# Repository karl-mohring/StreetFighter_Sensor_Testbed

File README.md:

# StreetFighter - Smart Streetlight Testbed

# What is it?
StreetFighter is a smart cities sensor platform intended for mounting inside LED street lights. The platform includes sensors to monitor road usage, and can manage street light dimming to adapt the light level to real-time traffic.

## Why the stupid name?
- The main hardware platform of this project is the Arduino **Yun**.
- **Yun** (Lee) is a character from CAPCOM's **Street Fighter** franchise.
- Our sensor platform is intended for road-side deployment in **street** lights to **fight** energy waste
- It made sense to me...

# [Quick Start](https://github.com/Leenix/StreetFighter_Sensor_Testbed/wiki/Hardware-Installation)
The phrase "quick-start" can be misleading in hardware projects, but here's a list of things you'll need to set up this platform [(Full details in the Wiki)](https://github.com/Leenix/StreetFighter_Sensor_Testbed/wiki):
- Arduino Yun (with 4GB card) or Arduino Leonardo (for the non-logging, non-WiFi version)
- StreetFighter PCB
- Traffic sensors (sonar, lidar, PIR)
- Environmental sensors (temperature, humidity, illuminance, IR temperature, noise)
- Some kind of long-range network transceiver (XBee socket)

After you get all all that, you just need to populate the PCBs, wire up the sensors, configure the Yun software, build and upload the Arduino-side firmware, power the platform somehow, and then you're golden.

# [Features](https://github.com/Leenix/StreetFighter_Sensor_Testbed/wiki/Features)
## Traffic detection
- PIR sensor detects generic movements from vehicles, cyslists, and pedestrians
- Sonar/Lidar counts vehicles over a single lane

## Environmental monitoring
- Ambient temperature
- Relative humidity
- Illuminance
- Ambient noise
- Road temperature
- Road flood level

## Lamp health and control
- Luminaire temperature
- Power consumption
- Dimming interface

## Other
- Smartphone detection using Wifi and/or Bluetooth
- Public WiFi AP (if wired connection is provided)

# [Documentation](https://github.com/Leenix/StreetFighter_Sensor_Testbed/wiki)
- Full installation documentation can be found on the [Wiki](https://github.com/Leenix/StreetFighter_Sensor_Testbed/wiki)
- Code documentation is inside the code. No external reference just yet.

# [License](http://www.gnu.org/licenses/gpl-3.0.en.html)

This project is licensed under the terms of the GNU General Public License v3.0.

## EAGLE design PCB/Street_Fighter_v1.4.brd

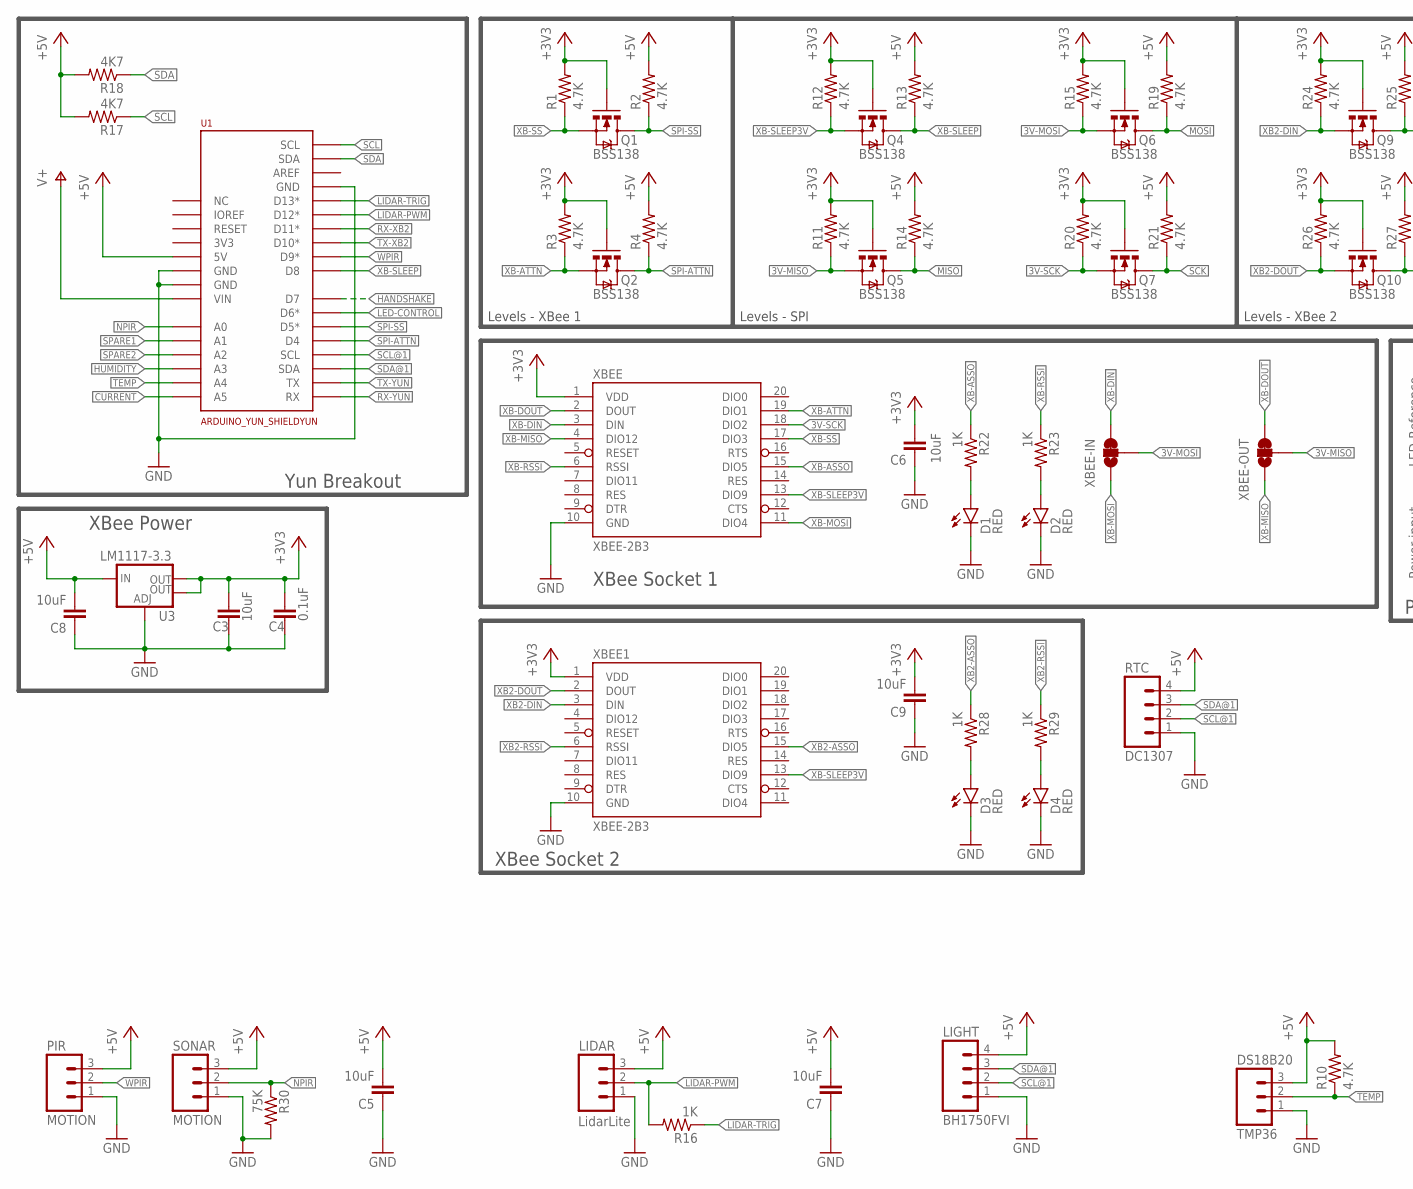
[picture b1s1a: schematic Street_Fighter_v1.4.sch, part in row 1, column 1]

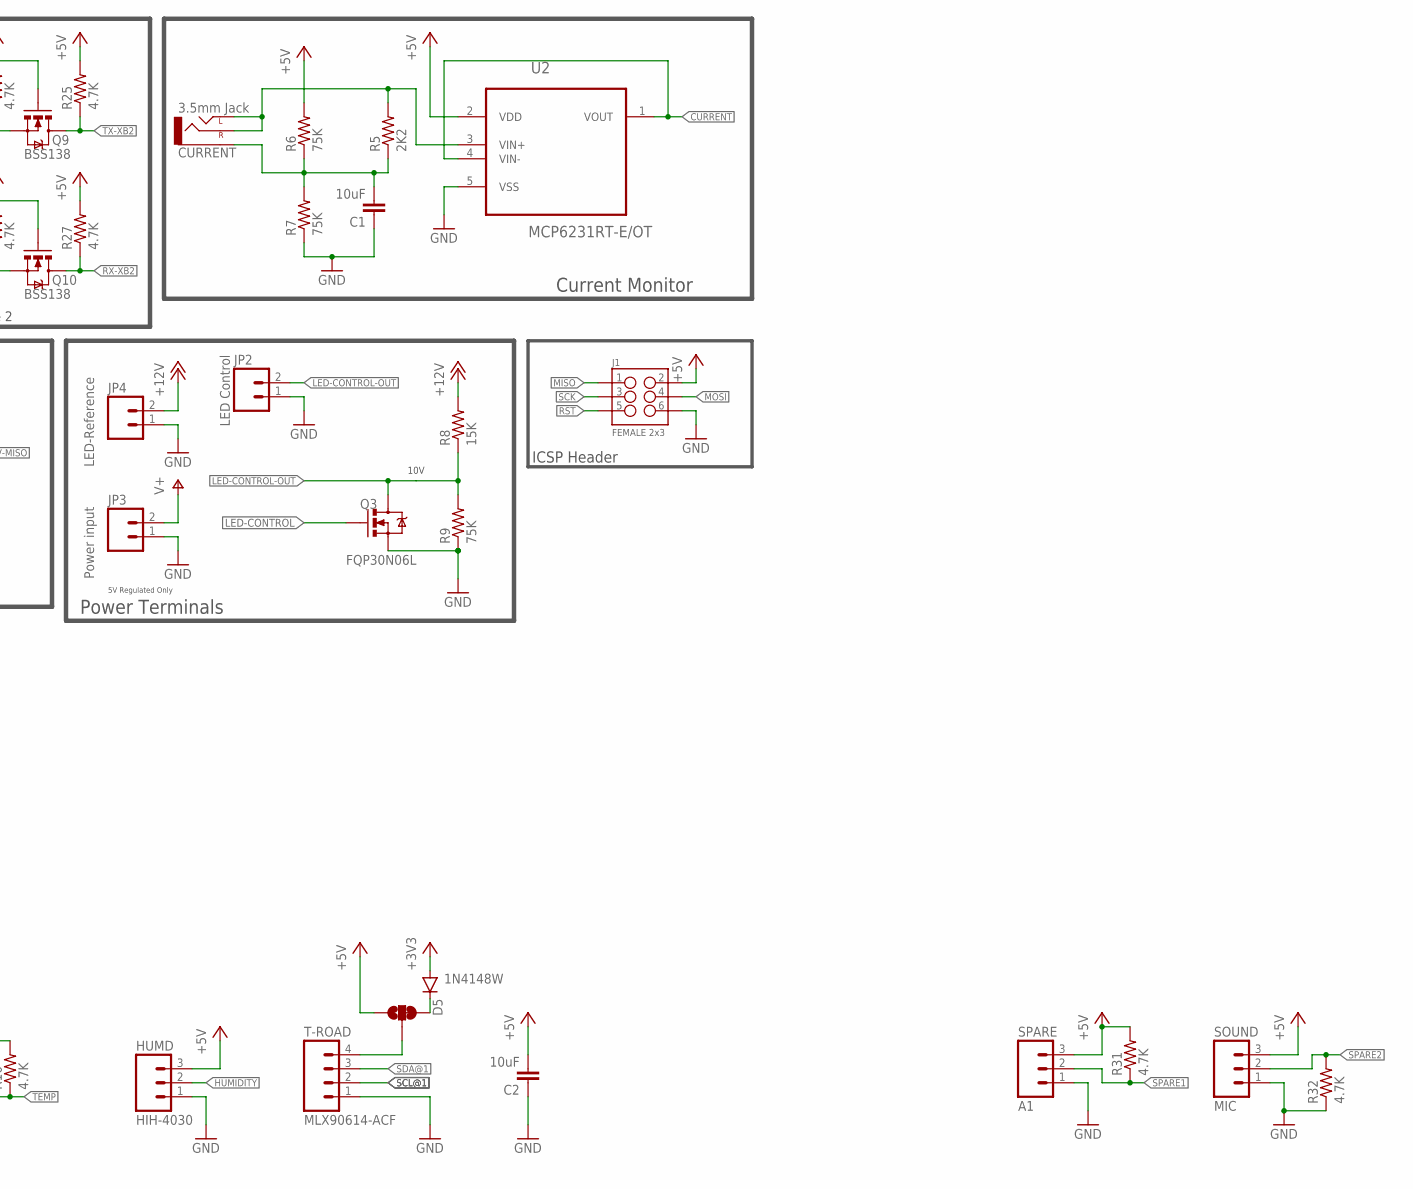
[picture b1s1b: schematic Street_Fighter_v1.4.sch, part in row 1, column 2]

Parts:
C1, C2, C3, C5, C6, C7, C8, C9: 10uF; 1206
C4: 0.1uF; 1206
CURRENT: 3.5mm Jack; AUDIO-JACK
D1, D2, D3, D4: RED; LED-1206
D5: 1N4148W; SOD-123
DS18B20: TMP36; 1X03
HUMD: HIH-4030; 1X03
J1: FEMALE 2x3; 2X3
JP2: LED Control; 1X02_LONGPADS
JP3: Power input; 1X02_LONGPADS
JP4: LED-Reference; 1X02_LONGPADS
LIDAR: LidarLite; 1X03
LIGHT: BH1750FVI; 1X04
PIR: MOTION; 1X03
Q1, Q2, Q4, Q5, Q6, Q7, Q9, Q10: BSS138; SOT23
Q3: FQP30N06L; TO220V
R1, R2, R3, R4, R10, R11, R12, R13, R14, R15, R19, R20, R21, R24, R25, R26, R27, R31, R32: 4.7K; 1206
R5: 2K2; 1206
R6, R7, R9, R30: 75K; 1206
R8: 15K; 1206
R16, R22, R23, R28, R29: 1K; 1206
R17, R18: 4K7; 1206
RTC: DC1307; 1X04
SONAR: MOTION; 1X03
SOUND: MIC; 1X03
SPARE: A1; 1X03
T-ROAD: MLX90614-ACF; 1X04
U1: ARDUINO_YUN_SHIELDYUN; DUEMILANOVE_VIAS
U2: MCP6231RT-E/OT; SOT95P270X145-5N
U3: LM1117-3.3; SOT223
XBEE, XBEE1: XBEE-2B3; XBEE-SMD
XBEE-IN: JUMPER-PAD-3-2OF3_NC_BY_TRACE_SMALL; PAD-JUMPER-3-2OF3_NC_BY_TRACE_YES_SILK_FULL_BOX
XBEE-OUT, XBEE-OUT1: JUMPER-PAD-3-2OF3_NC_BY_TRACE_SMALL; PAD-JUMPER-3-2OF3_NC_BY_TRACE_YES_SILK_FULL_BOX

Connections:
3V3: U1.3V3
3V-MISO: Q5.2 (S), R11.1, XBEE-OUT.2
3V-MOSI: Q6.2 (S), R15.1, XBEE-IN.2
3V-SCK: Q7.2 (S), R20.1, XBEE.18 (DIO2)
+3V3: C3.2, C4.2, C6.2, C9.2, D5.A, Q1.1 (G), Q2.1 (G), Q4.1 (G), Q5.1 (G), Q6.1 (G), Q7.1 (G), Q9.1 (G), Q10.1 (G), R1.2, R3.2, R11.2, R12.2, R15.2, R20.2, R24.2, R26.2, U3.2 (OUT), U3.4 (OUT), XBEE.1 (VDD), XBEE1.1 (VDD)
+5V: C2.2, C5.2, C7.2, C8.2, DS18B20.3, HUMD.3, J1.2, LIDAR.3, LIGHT.4, PIR.3, R2.2, R4.2, R6.2, R10.2, R13.2, R14.2, R17.2, R18.2, R19.2, R21.2, R25.2, R27.2, R31.2, RTC.4, SONAR.3, SOUND.3, SPARE.3, U1.5V, U2.2 (VDD), U3.3 (IN), XBEE-OUT1.1
+12V: JP4.2, R8.2
CURRENT: U1.A5, U2.1 (VOUT), U2.4 (VIN-)
GND: C1.1, C2.1, C3.1, C4.1, C5.1, C6.1, C7.1, C8.1, C9.1, D1.C, D2.C, D3.C, D4.C, DS18B20.1, HUMD.1, J1.6, JP2.1, JP3.1, JP4.1, LIDAR.1, LIGHT.1, PIR.1, Q3.3 (S), R7.1, R9.1, R30.2, R32.1, RTC.1, SONAR.1, SOUND.1, SPARE.1, T-ROAD.1, U1.GND, U1.GND@0 (GND), U1.GND@1 (GND), U2.5 (VSS), U3.1 (ADJ), XBEE.10 (GND), XBEE1.10 (GND)
HANDSHAKE: U1.7 (D7)
HUMIDITY: HUMD.2, U1.A3
LED-CONTROL: Q3.1 (G), U1.6 (D6*)
LED-CONTROL-OUT: JP2.2, Q3.2 (D), R8.1, R9.2
LIDAR-PWM: LIDAR.2, R16.2, U1.12 (D12*)
LIDAR-TRIG: R16.1, U1.13 (D13*)
MISO: J1.1, Q5.3 (D), R14.1
MOSI: J1.4, Q6.3 (D), R19.1
unnamed: D1.A, R22.2
unnamed: CURRENT.RING (RIGHT), CURRENT.TIP (LEFT), R5.2, U2.3 (VIN+)
unnamed: D2.A, R23.2
unnamed: C1.2, CURRENT.SLEEVE, R5.1, R6.1, R7.2
unnamed: D3.A, R28.2
unnamed: D4.A, R29.2
unnamed: D5.C, XBEE-OUT1.3
unnamed: T-ROAD.4, XBEE-OUT1.2
NPIR: R30.1, SONAR.2, U1.A0
RST: J1.5
RX-XB2: Q10.3 (D), R27.1, U1.11 (D11*)
RX-YUN: U1.0 (RX)
SCK: J1.3, Q7.3 (D), R21.1
SCL: R17.1, U1.3@1 (SCL)
SCL@1: LIGHT.2, RTC.2, T-ROAD.2, U1.3 (SCL)
SDA: R18.1, U1.2@1 (SDA)
SDA@1: LIGHT.3, RTC.3, T-ROAD.3, U1.2 (SDA)
SPARE1: R31.1, SPARE.2, U1.A1
SPARE2: R32.2, SOUND.2, U1.A2
SPI-ATTN: Q2.3 (D), R4.1, U1.D4
SPI-SS: Q1.3 (D), R2.1, U1.5 (D5*)
TEMP: DS18B20.2, R10.1, U1.A4
TX-XB2: Q9.3 (D), R25.1, U1.10 (D10*)
TX-YUN: U1.1 (TX)
V+: JP3.2, U1.VIN
WPIR: PIR.2, U1.9 (D9*)
XB2-ASSO: R28.1, XBEE1.15 (DIO5)
XB2-DIN: Q9.2 (S), R24.1, XBEE1.3 (DIN)
XB2-DOUT: Q10.2 (S), R26.1, XBEE1.2 (DOUT)
XB2-RSSI: R29.1, XBEE1.6 (RSSI)
XB-ASSO: R22.1, XBEE.15 (DIO5)
XB-ATTN: Q2.2 (S), R3.1, XBEE.19 (DIO1)
XB-DIN: XBEE.3 (DIN), XBEE-IN.3
XB-DOUT: XBEE.2 (DOUT), XBEE-OUT.3
XB-MISO: XBEE.4 (DIO12), XBEE-OUT.1
XB-MOSI: XBEE.11 (DIO4), XBEE-IN.1
XB-RSSI: R23.1, XBEE.6 (RSSI)
XB-SLEEP: Q4.3 (D), R13.1, U1.8 (D8)
XB-SLEEP3V: Q4.2 (S), R12.1, XBEE.13 (DIO9), XBEE1.13 (DIO9)
XB-SS: Q1.2 (S), R1.1, XBEE.17 (DIO3)

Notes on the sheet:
10V
Power Terminals
Yun Breakout
Current Monitor
XBee Socket 1
5V Regulated Only
Levels - XBee 1
Levels - SPI
Levels - XBee 2
XBee Power
XBee Socket 2
ICSP Header

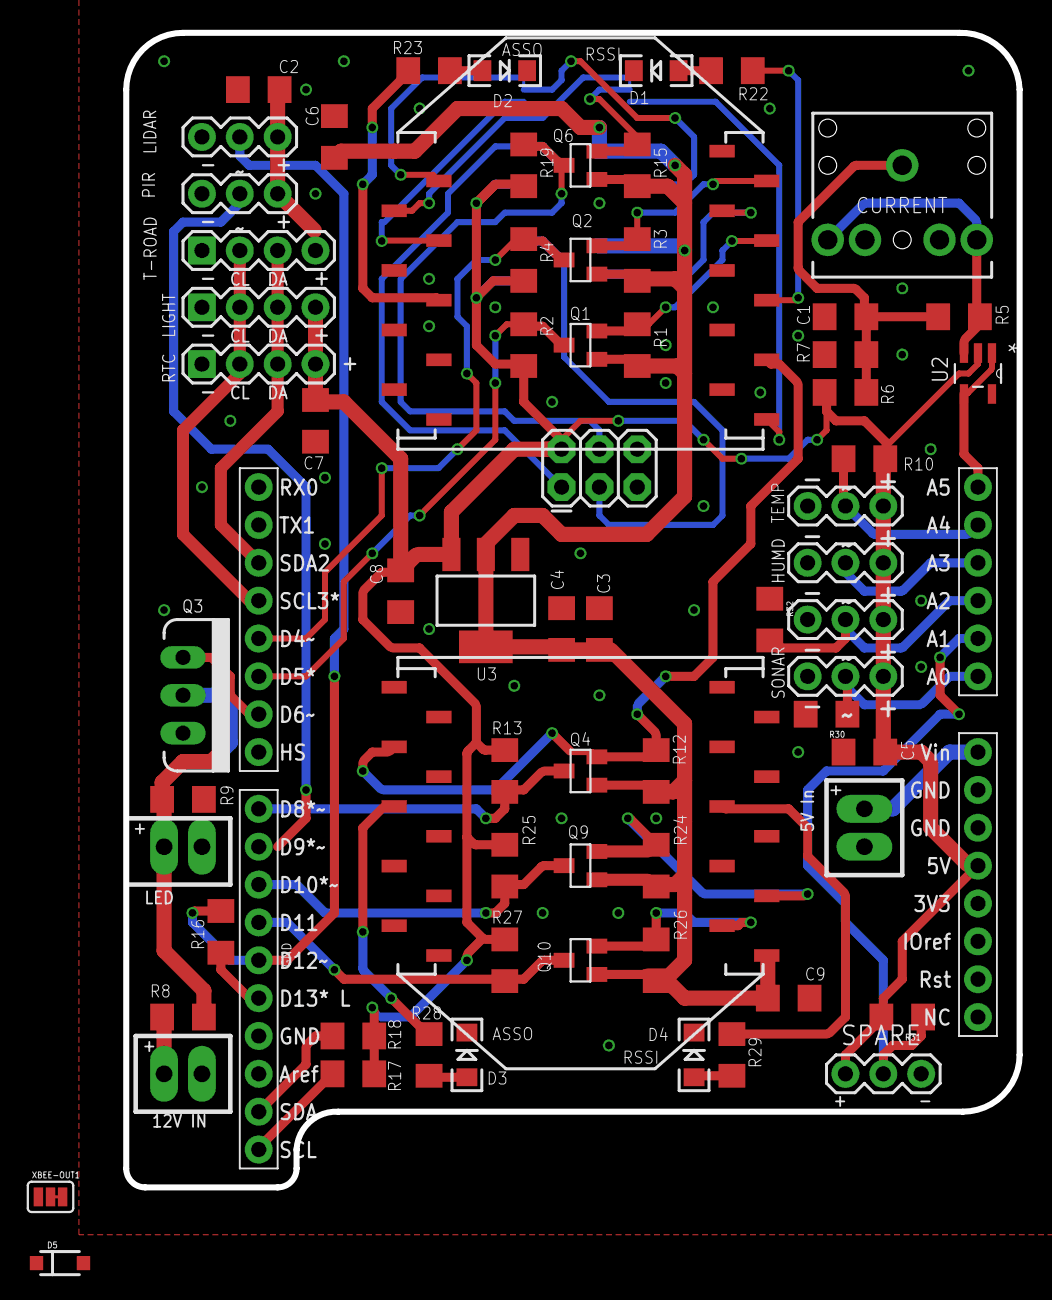
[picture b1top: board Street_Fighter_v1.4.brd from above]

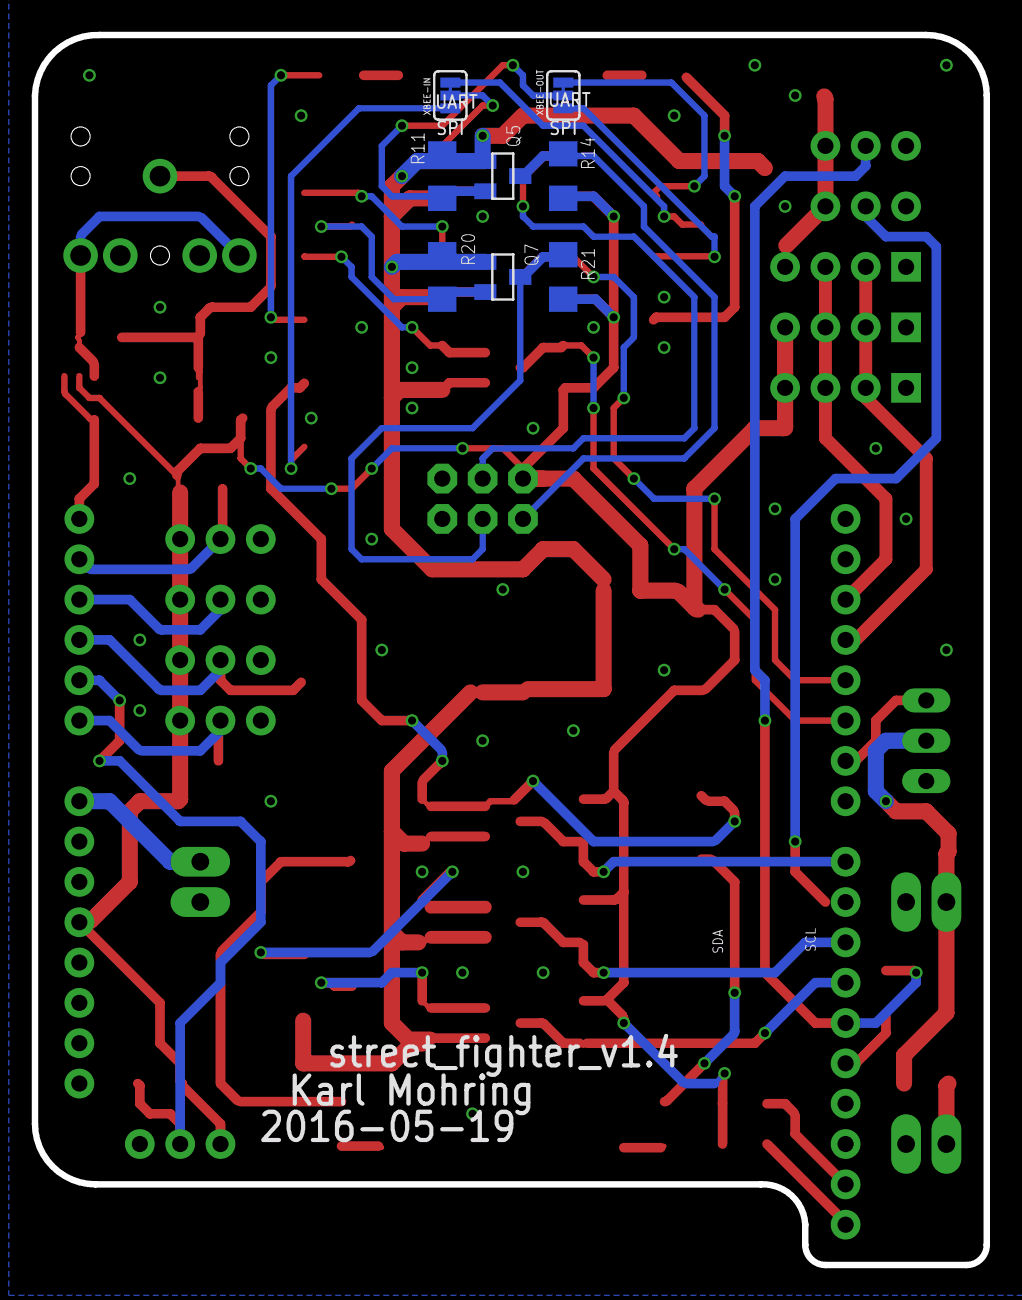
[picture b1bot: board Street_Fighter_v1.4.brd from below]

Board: 2 copper layers, 59.9 x 77.5 mm, 78 parts (8 on the bottom side), 52 nets.

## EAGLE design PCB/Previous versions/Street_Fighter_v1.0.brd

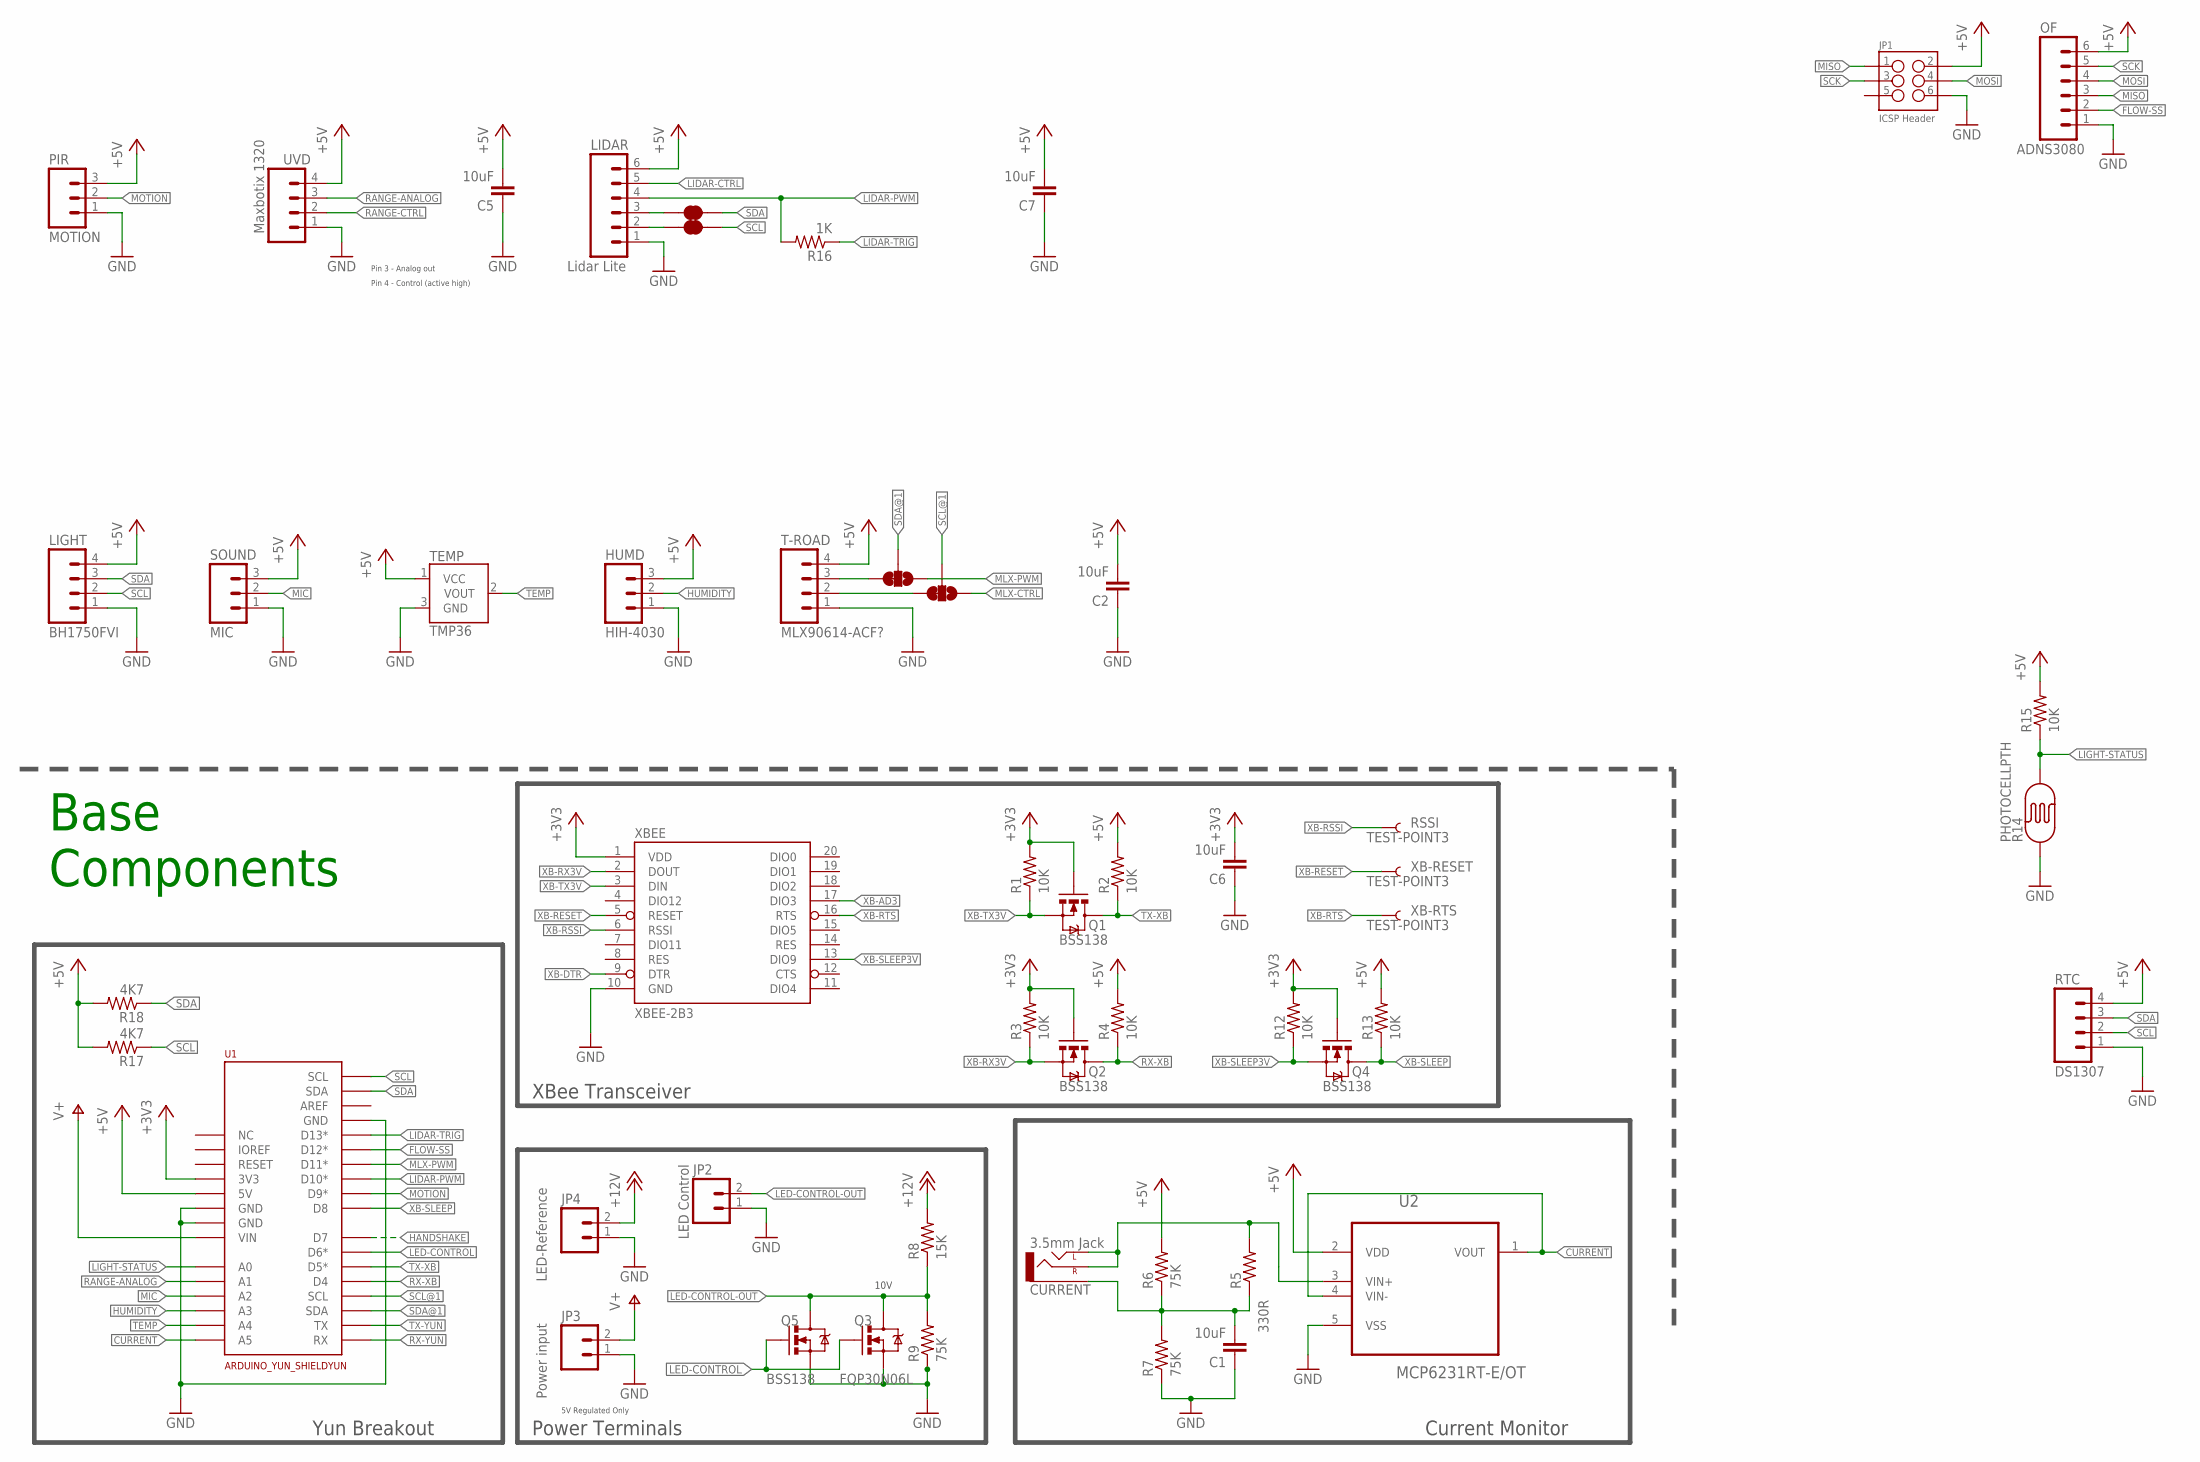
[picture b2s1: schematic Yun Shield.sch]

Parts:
C1, C2, C5, C6, C7: 10uF; 1206
CURRENT: 3.5mm Jack; AUDIO-JACK
HUMD: HIH-4030; 1X03
JP1: ICSP Header; 2X3
JP2: LED Control; 1X02_LONGPADS
JP3: Power input; 1X02_LONGPADS
JP4: LED-Reference; 1X02_LONGPADS
LIDAR: Lidar Lite; 1X06
LIGHT: BH1750FVI; 1X04
OF: ADNS3080; 1X06
PIR: MOTION; 1X03
Q1, Q2, Q4, Q5: BSS138; SOT23
Q3: FQP30N06L; TO220V
R1, R2, R3, R4, R12, R13, R15: 10K; 1206
R5: 330R; 1206
R6, R7, R9: 75K; 1206
R8: 15K; 1206
R14: PHOTOCELLPTH; PHOTOCELL
R16: 1K; 1206
R17, R18: 4K7; 1206
RSSI: TEST-POINT3; PAD.03X.03
RTC: DS1307; 1X04
SJ1, SJ2: JUMPER-PAD-2-NC_BY_TRACE; PAD-JUMPER-2-NC_BY_TRACE_YES_SILK
SJ3, SJ4: JUMPER-PAD-3-2OF3_NC_BY_TRACE_SMALL; PAD-JUMPER-3-2OF3_NC_BY_TRACE_YES_SILK_FULL_BOX
SOUND: MIC; 1X03
T-ROAD: MLX90614-ACF?; 1X04
TEMP: TMP36; TO-92
U1: ARDUINO_YUN_SHIELDYUN; DUEMILANOVE_VIAS
U2: MCP6231RT-E/OT; SOT95P270X145-5N
UVD: Maxbotix 1320; 1X04
XB-RESET: TEST-POINT3; PAD.03X.03
XB-RTS: TEST-POINT3; PAD.03X.03
XBEE: XBEE-2B3; XBEE-SMD

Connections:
+3V3: C6.2, Q1.1 (G), Q2.1 (G), Q4.1 (G), R1.2, R3.2, R12.2, U1.3V3, XBEE.1 (VDD)
+5V: C2.2, C5.2, C7.2, HUMD.3, JP1.2, LIDAR.6, LIGHT.4, OF.6, PIR.3, R2.2, R4.2, R6.2, R13.2, R15.2, R17.2, R18.2, RTC.4, SOUND.3, T-ROAD.4, TEMP.1 (VCC), U1.5V, U2.2 (VDD), UVD.4
+12V: JP4.2, R8.2
CURRENT: U1.A5, U2.1 (VOUT), U2.4 (VIN-)
FLOW-SS: OF.2, U1.12 (D12*)
GND: C1.1, C2.1, C5.1, C6.1, C7.1, HUMD.1, JP1.6, JP2.1, JP3.1, JP4.1, LIDAR.1, LIGHT.1, OF.1, PIR.1, Q3.3 (S), Q5.2 (S), R7.1, R9.1, R14.1, RTC.1, SOUND.1, T-ROAD.1, TEMP.3 (GND), U1.GND, U1.GND@0 (GND), U1.GND@1 (GND), U2.5 (VSS), UVD.1, XBEE.10 (GND)
HANDSHAKE: U1.7 (D7)
HUMIDITY: HUMD.2, U1.A3
LED-CONTROL: Q3.1 (G), Q5.1 (G), U1.6 (D6*)
LED-CONTROL-OUT: JP2.2, Q3.2 (D), Q5.3 (D), R8.1, R9.2
LIDAR-CTRL: LIDAR.5
LIDAR-PWM: LIDAR.4, R16.2, U1.10 (D10*)
LIDAR-TRIG: R16.1, U1.13 (D13*)
LIGHT-STATUS: R14.2, R15.1, U1.A0
MIC: SOUND.2, U1.A2
MISO: JP1.1, OF.3
MLX-CTRL: SJ4.1
MLX-PWM: SJ3.1, U1.11 (D11*)
MOSI: JP1.4, OF.4
MOTION: PIR.2, U1.9 (D9*)
unnamed: CURRENT.RING (RIGHT), CURRENT.TIP (LEFT), R5.2, U2.3 (VIN+)
unnamed: C1.2, CURRENT.SLEEVE, R5.1, R6.1, R7.2
RANGE-ANALOG: U1.A1, UVD.3
RANGE-CTRL: UVD.2
RX-XB: Q2.3 (D), R4.1, U1.D4
RX-YUN: U1.0 (RX)
SCK: JP1.3, OF.5
SCL: LIDAR.2, LIGHT.2, R17.1, RTC.2, SJ2.1, SJ2.2, U1.3@1 (SCL)
SCL@1: SJ4.2, SJ4.3, T-ROAD.2, U1.3 (SCL)
SDA: LIDAR.3, LIGHT.3, R18.1, RTC.3, SJ1.1, SJ1.2, U1.2@1 (SDA)
SDA@1: SJ3.2, SJ3.3, T-ROAD.3, U1.2 (SDA)
TEMP: TEMP.2 (VOUT), U1.A4
TX-XB: Q1.3 (D), R2.1, U1.5 (D5*)
TX-YUN: U1.1 (TX)
V+: JP3.2, U1.VIN
XB-AD3: XBEE.17 (DIO3)
XB-DTR: XBEE.9 (DTR)
XB-RESET: XB-RESET.P$1, XBEE.5 (RESET)
XB-RSSI: RSSI.P$1, XBEE.6 (RSSI)
XB-RTS: XB-RTS.P$1, XBEE.16 (RTS)
XB-RX3V: Q2.2 (S), R3.1, XBEE.2 (DOUT)
XB-SLEEP: Q4.3 (D), R13.1, U1.8 (D8)
XB-SLEEP3V: Q4.2 (S), R12.1, XBEE.13 (DIO9)
XB-TX3V: Q1.2 (S), R1.1, XBEE.3 (DIN)

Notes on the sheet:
10V
Pin 3 - Analog out
Pin 4 - Control (active high)
Power Terminals
Yun Breakout
Current Monitor
XBee Transceiver
Base Components
5V Regulated Only

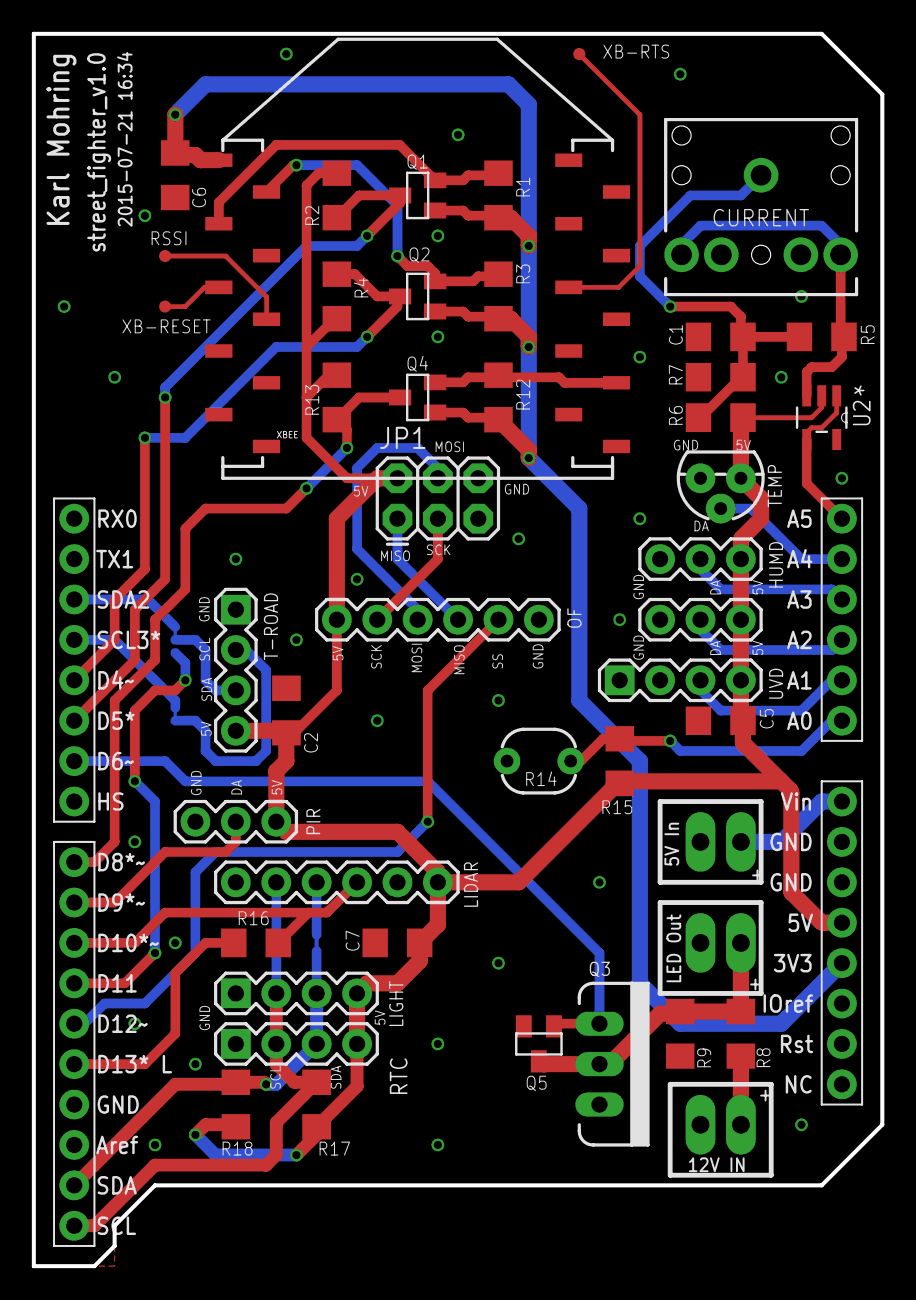
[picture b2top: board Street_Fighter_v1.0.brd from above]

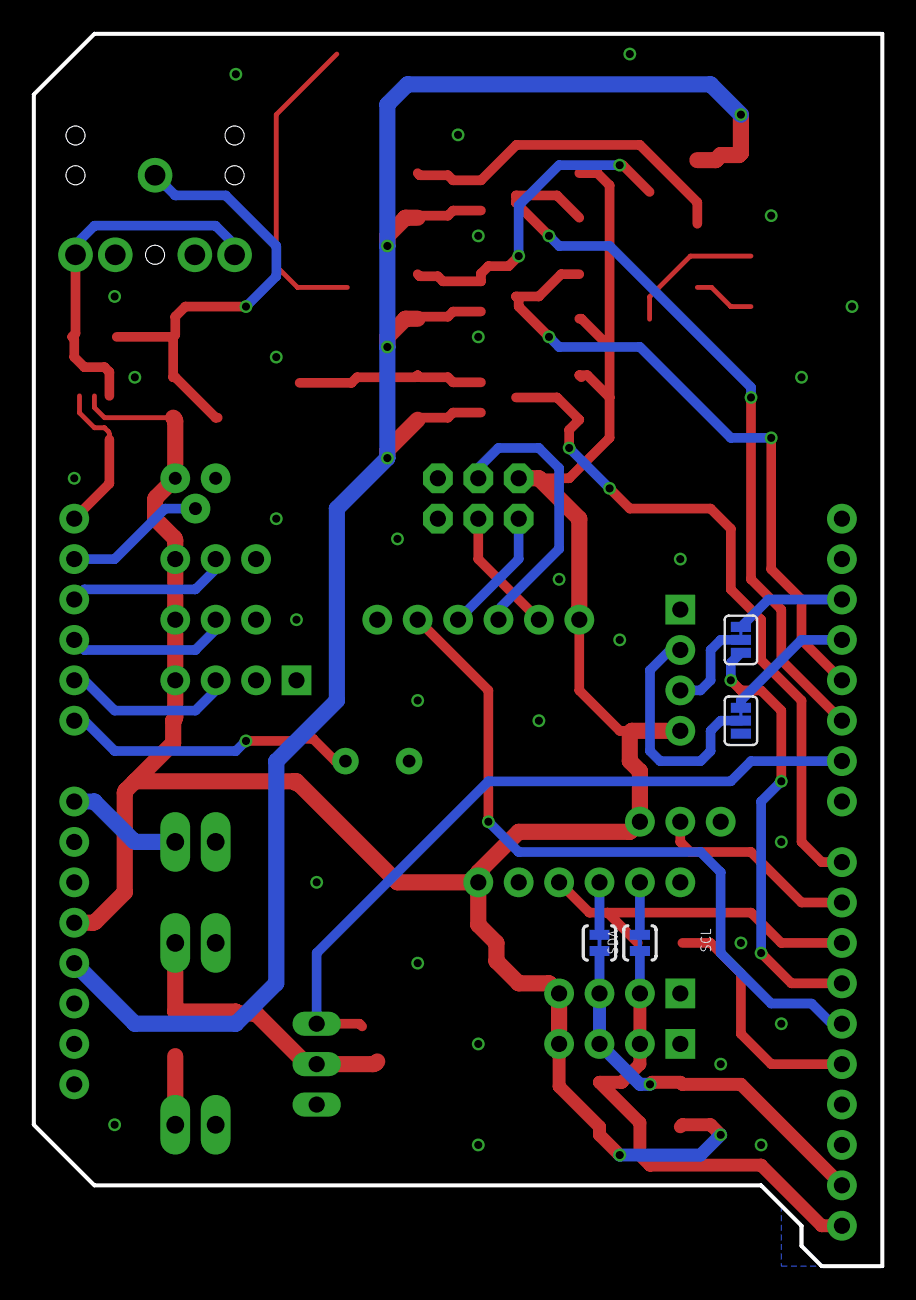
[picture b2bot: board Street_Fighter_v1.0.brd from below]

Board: 2 copper layers, 53.3 x 77.5 mm, 51 parts (4 on the bottom side), 36 nets.

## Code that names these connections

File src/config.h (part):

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const byte LAMP_CONTROL_PIN = 6;    // Lamp control - uses PWM with inverse duty cycle
const byte YUN_HANDSHAKE_PIN = 7;   // Yun handshake - HIGH when Yun is busy/booting
const byte XBEE_SLEEP_PIN = 8;      // XBEE sleep pin; Bring HIGH to allow XBEE comms
const byte WIDE_PIR_PIN_L = 9;      // PIR motion detect pin; pulled HIGH when motion is detected
const byte COMM_2_TX = 10;          // Send pin for XBEE socket 2; UART-only
const byte COMM_2_RX = 11;          // Receive pin for XBEE socket 2; UART-only
const byte LIDAR_PWM_PIN = 12;      // Data pin for LIDARLite
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const byte COMM_1_TX = 16;          // Receive pin for XBEE socket 1; UART and SPI compatible
const byte WIDE_PIR_PIN_R = A0;     // Sonar receive pin - can use pulse width or ADC for distance measurements
const byte NARROW_PIR_PIN = A1;
const byte HUMIDITY_PIN = A3;        // Humidity level pin - Gives ADC humidity level
const byte TEMPERATURE_PIN = A4;     // Temperature data pin for DS18B20 digital temperature probe
const byte CURRENT_DETECT_PIN = A5;  // Current monitor pin for current clamp - gives offset ADC current wave

///////////////////////////////////////////////////////////////////////////////
// Timer
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
///////////////////////////////////////////////////////////////////////////////
// Current Monitor
const int TRANSFORMER_RATIO = 2000;  // The ratio of the current transformer
const int BURDEN_RESISTOR = 2200;    // Value of the burden resistor in Ohms
const int CURRENT_SAMPLES = 1000;    // Number of ADC samples taken when measuring current
const double CURRENT_CALIBRATION_FACTOR = TRANSFORMER_RATIO / BURDEN_RESISTOR;

///////////////////////////////////////////////////////////////////////////////
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
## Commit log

2015-08-14 :circus_tent: Added .gitattributes & .gitignore files
2015-08-14 Initial commit - All sensors added
    Still need XBee and current sensor hardware
2016-01-14 V5 Update
    Added 3D printed parts
    V5 - Trialling new Sonar detection algorithm
    - Sonar must have 2 consecutive detections to register
    PIR timeout changed from 5s to 2s.
2016-01-22 Added debug mode to code
    We're actually up to version 6
    - Fixed the angular printed mount for lidar
2016-01-22 Fixed baud rate
2016-01-26 Version 7 - Now with dimming control
    Added in lamp dimming functions
    Traffic entries prompt the lamp to activate
    Disable lamp control by commenting out the startLampControl function in
    setup
2016-01-29 Fixed Sonar counting
2016-02-22 Version 8 - Refactored code to use data structure instead of JSON - Added dimming functions - Fixed JSON Printing
2016-02-22 Added support for both TMP36 and DS18B20 - Change temperature sensor type in the config file
2016-02-23 Fixed memory leak - Print to XBee function is broken - Added quick function to logging to get the log level
2016-02-24 Fixed memory leak with xbee buffer - Buffer now deallocates after use * Dynamic memory allocation is prohibited on aviation software where it could cause a safety issue * May need to make all buffers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
2016-02-26 Converted dynamic buffers to static - Some sensors start with an update so no data is missing after a restart - Changed temperature sensor over to DS18B20
2016-04-08 Create gh-pages branch via GitHub
2016-04-11 Improved readme file
2016-04-14 Added license. Ignoring SKB files
2016-04-18 Removed XBEE API code; now using transparent mode
2016-04-18 Initialised new branch for operating unit (Orobas)
2016-04-18 Fixed Flauros developmental branch for prototype
2016-04-18 Deleted Tags
2016-04-18 Changed feature list in readme
2016-04-18 Changed readme levels for web page
2016-04-18 added picture to readme
2016-04-29 Fixes Issue #2 and Issue #4. New XBee socket + SPI
2016-04-29 Added travis-ci badge
2016-04-29 Added title
2016-04-29 Switched to adafruit RTC library
2016-04-29 Fixed sonar pin assignment
2016-04-29 Removed unused sonar library
2016-05-10 Added spare header to board
2016-05-11 Shuffled libraries
2016-05-11 Temporary delete of troubled library folders
2016-05-11 Readded problem libraries
2016-05-11 Added arduino badge
2016-06-07 StreetFighter v1.3 board - Fixed bad pin assignments for SoftSerial
2016-06-07 Fixed gitignore - had reverted
2016-06-07 Removing ignored files
2016-06-09 Added bluetooth scanner functions
2016-06-10 Added flags for optional sensors
2016-06-15 Changed RTC to DS3231; Timestamp now in ISO format
2016-06-16 Added analog sonar option; hopefully fixed bluetooth scanning
2016-06-20 Expanded SoftSerial buffer; Optimised bluetooth scan string
2016-08-18 Fixed sonar reads - Sonar now only performs compensation in pulseIn mode - There may be bugs in the compensation algorithm due to numerical overflows - Analog measurements just follow the usual scali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
2016-11-16 Updated mounting plate for traffic sensors. Also started adding in the possibility for more than 2 PIR sensors.
2016-11-16 Fixed up some import errors; not completely
2016-11-17 Fixed up PIR sensor behaviour
2016-11-23 Rewrote the MLX90621 library to use much less RAM.
2016-11-24 Added bluetooth, JSON, and XBee back in
2017-02-08 Cleaned up redundant libraries
2017-02-08 Switched PCB from EagleCAD to KiCAD - Started transferring things from Yun to LoPy
2017-02-08 Schematic didn't take last time?
2017-02-24 Formatted config file
2017-03-09 Switched over to PIR library
2017-03-14 Switch the lidar to use the tripwire lib
2017-06-14 Fixed tripwire cooldowns

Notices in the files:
README.md:
http://www.gnu.org/graphics/gplv3-127x51.png
parts and their libraries:
SparkFun-Capacitors: Licensing: Creative Commons ShareAlike 4.0 International - https://creativecommons.org/licenses/by-sa/4.0
SparkFun-Boards: Licensing: CC v3.0 Share-Alike You are welcome to use this library for commercial purposes.
